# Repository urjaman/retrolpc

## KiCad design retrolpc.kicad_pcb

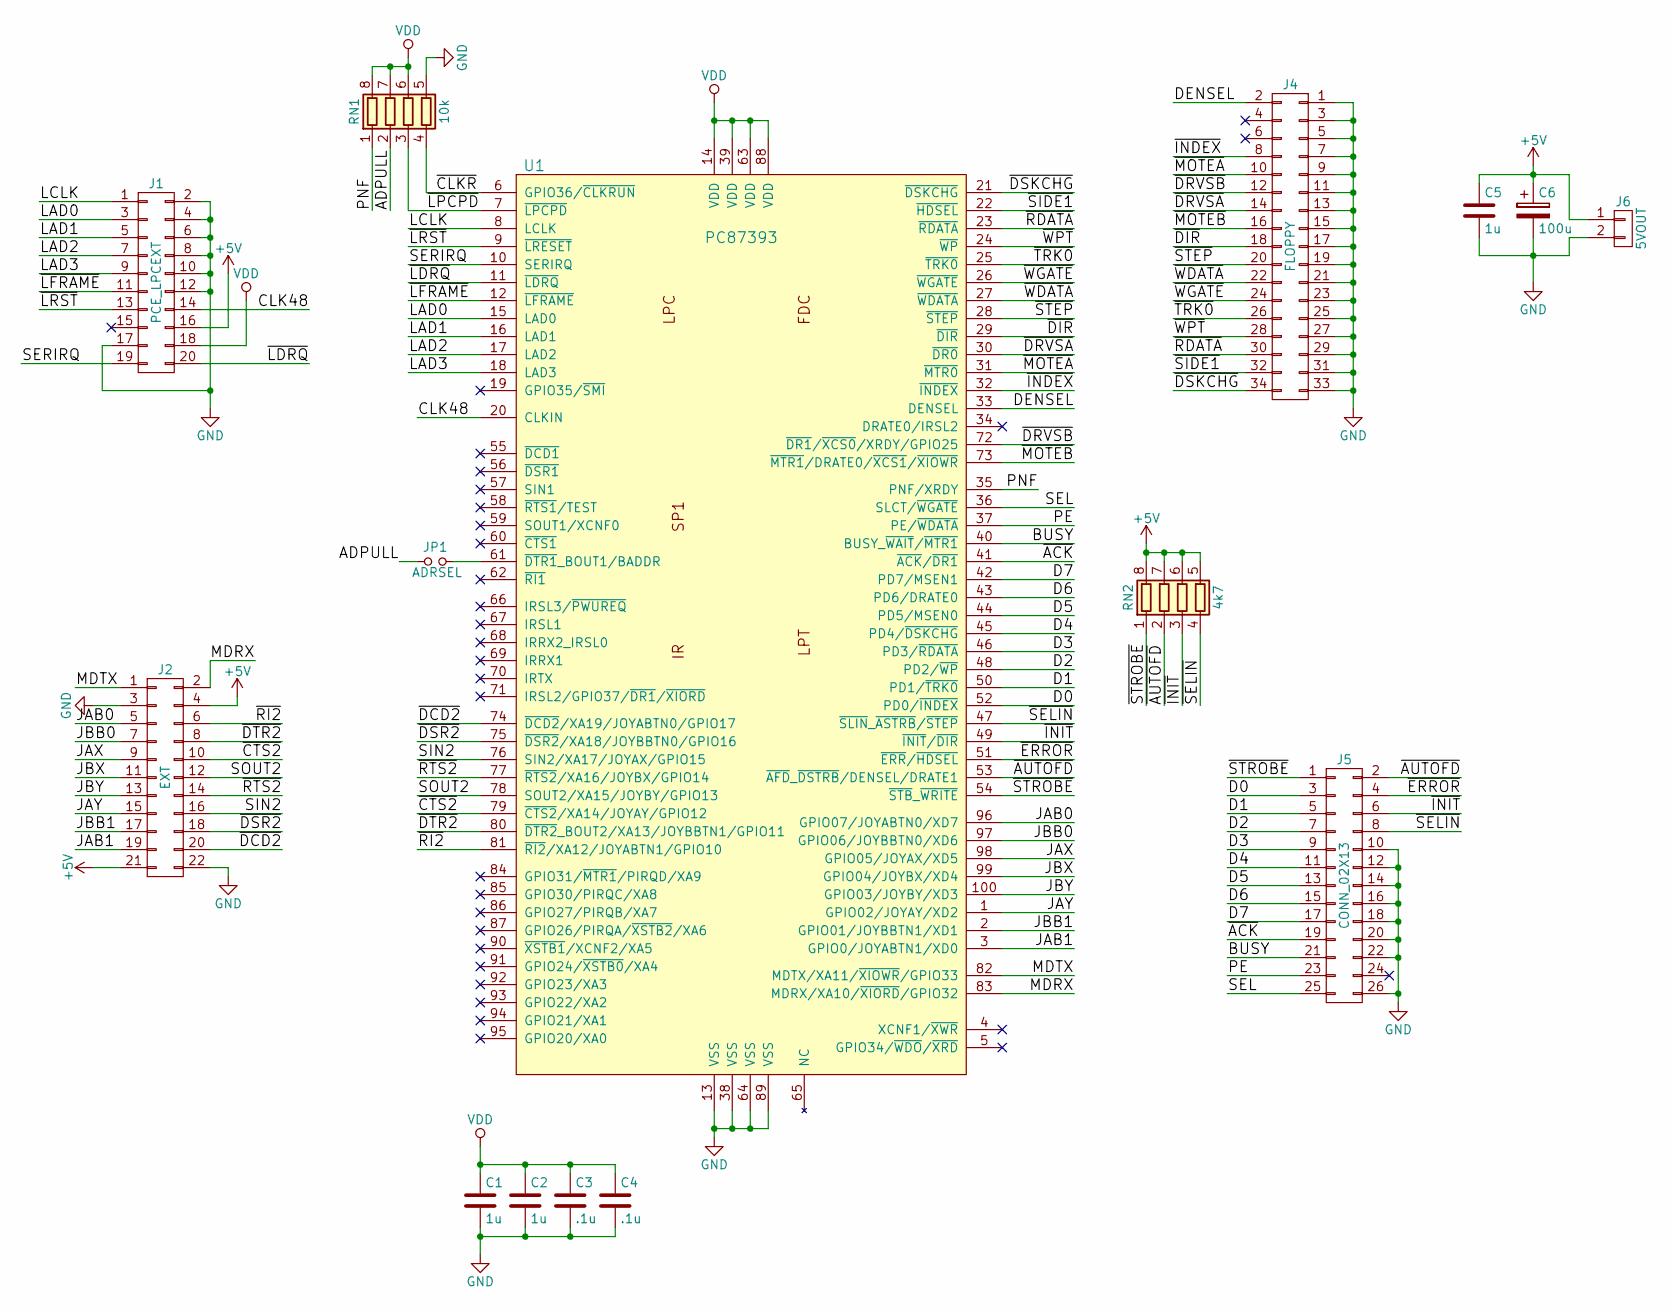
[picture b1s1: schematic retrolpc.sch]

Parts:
C1, C2, C5: 1u; C_0805_HandSoldering
C3, C4: .1u; C_0603_HandSoldering
C6: 100u; CP_Radial_D8.0mm_P3.50mm
J1: PCE_LPCEXT; Socket_Strip_Straight_2x10_Pitch2.54mm
J2: EXT; Pin_Header_Straight_2x11_Pitch2.54mm
J4: FLOPPY; Pin_Header_Straight_2x17_Pitch2.54mm
J5: CONN_02X13; Pin_Header_Straight_2x13_Pitch2.54mm
J6: 5VOUT; TerminalBlock_Pheonix_PT-3.5mm_2pol
JP1: ADRSEL; Pin_Header_Straight_1x02_Pitch2.54mm
RN1: 10k; R_Array_Convex_4x0603
RN2: 4k7; R_Array_Convex_4x0603
U1: PC87393; TQFP-100_14x14mm_Pitch0.5mm

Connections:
+5V: C5.1, C6.1, J1.16, J2.4, J2.21, J6.1, RN2.5 (R4.2), RN2.6 (R3.2), RN2.7 (R2.2), RN2.8 (R1.2)
/ADPULL: JP1.1, RN1.2 (R2.1)
/BUSY: J5.21, U1.40 (BUSY_~WAIT~/~MTR1)
/CLK48: J1.14, U1.20 (CLKIN)
/D0: J5.3, U1.52 (PD0/~INDEX)
/D1: J5.5, U1.50 (PD1/~TRK0)
/D2: J5.7, U1.48 (PD2/~WP)
/D3: J5.9, U1.46 (PD3/~RDATA)
/D4: J5.11, U1.45 (PD4/~DSKCHG)
/D5: J5.13, U1.44 (PD5/MSEN0)
/D6: J5.15, U1.43 (PD6/DRATE0)
/D7: J5.17, U1.42 (PD7/MSEN1)
/DENSEL: J4.2, U1.33 (DENSEL)
/JAB0: J2.5, U1.96 (GPIO07/JOYABTN0/XD7)
/JAB1: J2.19, U1.3 (GPIO0/JOYABTN1/XD0)
/JAX: J2.9, U1.98 (GPIO05/JOYAX/XD5)
/JAY: J2.15, U1.1 (GPIO02/JOYAY/XD2)
/JBB0: J2.7, U1.97 (GPIO06/JOYBBTN0/XD6)
/JBB1: J2.17, U1.2 (GPIO01/JOYBBTN1/XD1)
/JBX: J2.11, U1.99 (GPIO04/JOYBX/XD4)
/JBY: J2.13, U1.100 (GPIO03/JOYBY/XD3)
/LAD0: J1.3, U1.15 (LAD0)
/LAD1: J1.5, U1.16 (LAD1)
/LAD2: J1.7, U1.17 (LAD2)
/LAD3: J1.9, U1.18 (LAD3)
/LCLK: J1.1, U1.8 (LCLK)
/MDRX: J2.2, U1.83 (MDRX/XA10/~XIORD~/GPIO32)
/MDTX: J2.1, U1.82 (MDTX/XA11/~XIOWR~/GPIO33)
/PE: J5.23, U1.37 (PE/~WDATA)
/PNF: RN1.1 (R1.1), U1.35 (PNF/XRDY)
/SEL: J5.25, U1.36 (SLCT/~WGATE)
/SERIRQ: J1.19, U1.10 (SERIRQ)
/SIN2: J2.16, U1.76 (SIN2/XA17/JOYAX/GPIO15)
/SOUT2: J2.12, U1.78 (SOUT2/XA15/JOYBY/GPIO13)
/~ACK: J5.19, U1.41 (~ACK~/~DR1)
/~AUTOFD: J5.2, RN2.2 (R2.1), U1.53 (~AFD~_~DSTRB~/DENSEL/DRATE1)
/~CLKR: RN1.4 (R4.1), U1.6 (GPIO36/~CLKRUN)
/~CTS2: J2.10, U1.79 (~CTS2~/XA14/JOYAY/GPIO12)
/~DCD2: J2.20, U1.74 (~DCD2~/XA19/JOYABTN0/GPIO17)
/~DIR: J4.18, U1.29 (~DIR)
/~DRVSA: J4.14, U1.30 (~DR0)
/~DRVSB: J4.12, U1.72 (~DR1~/~XCS0~/XRDY/GPIO25)
/~DSKCHG: J4.34, U1.21 (~DSKCHG)
/~DSR2: J2.18, U1.75 (~DSR2~/XA18/JOYBBTN0/GPIO16)
/~DTR2: J2.8, U1.80 (~DTR2~_BOUT2/XA13/JOYBBTN1/GPIO11)
/~ERROR: J5.4, U1.51 (~ERR~/~HDSEL)
/~INDEX: J4.8, U1.32 (~INDEX)
/~INIT: J5.6, RN2.3 (R3.1), U1.49 (~INIT~/~DIR)
/~LDRQ: J1.20, U1.11 (~LDRQ)
/~LFRAME: J1.11, U1.12 (~LFRAME)
/~LPCPD: RN1.3 (R3.1), U1.7 (~LPCPD)
/~LRST: J1.13, U1.9 (~LRESET)
/~MOTEA: J4.10, U1.31 (~MTR0)
/~MOTEB: J4.16, U1.73 (~MTR1~/DRATE0/~XCS1~/~XIOWR)
/~RDATA: J4.30, U1.23 (~RDATA)
/~RI2: J2.6, U1.81 (~RI2~/XA12/JOYABTN1/GPIO10)
/~RTS2: J2.14, U1.77 (~RTS2~/XA16/JOYBX/GPIO14)
/~SELIN: J5.8, RN2.4 (R4.1), U1.47 (~SLIN~_~ASTRB~/~STEP)
/~SIDE1: J4.32, U1.22 (~HDSEL)
/~STEP: J4.20, U1.28 (~STEP)
/~STROBE: J5.1, RN2.1 (R1.1), U1.54 (~STB~_~WRITE)
/~TRK0: J4.26, U1.25 (~TRK0)
/~WDATA: J4.22, U1.27 (~WDATA)
/~WGATE: J4.24, U1.26 (~WGATE)
/~WPT: J4.28, U1.24 (~WP)
GND: C1.2, C2.2, C3.2, C4.2, C5.2, C6.2, J1.2, J1.4, J1.6, J1.8, J1.10, J1.12, J1.17, J2.3, J2.22, J4.1, J4.3, J4.5, J4.7, J4.9, J4.11, J4.13, J4.15, J4.17, J4.19, J4.21, J4.23, J4.25, J4.27, J4.29, J4.31, J4.33, J5.10, J5.12, J5.14, J5.16, J5.18, J5.20, J5.22, J5.26, J6.2, RN1.5 (R4.2), U1.13 (VSS), U1.38 (VSS), U1.64 (VSS), U1.89 (VSS)
unnamed: JP1.2, U1.61 (~DTR1~_BOUT1/BADDR)
VDD: C1.1, C2.1, C3.1, C4.1, J1.18, RN1.6 (R3.2), RN1.7 (R2.2), RN1.8 (R1.2), U1.14 (VDD), U1.39 (VDD), U1.63 (VDD), U1.88 (VDD)

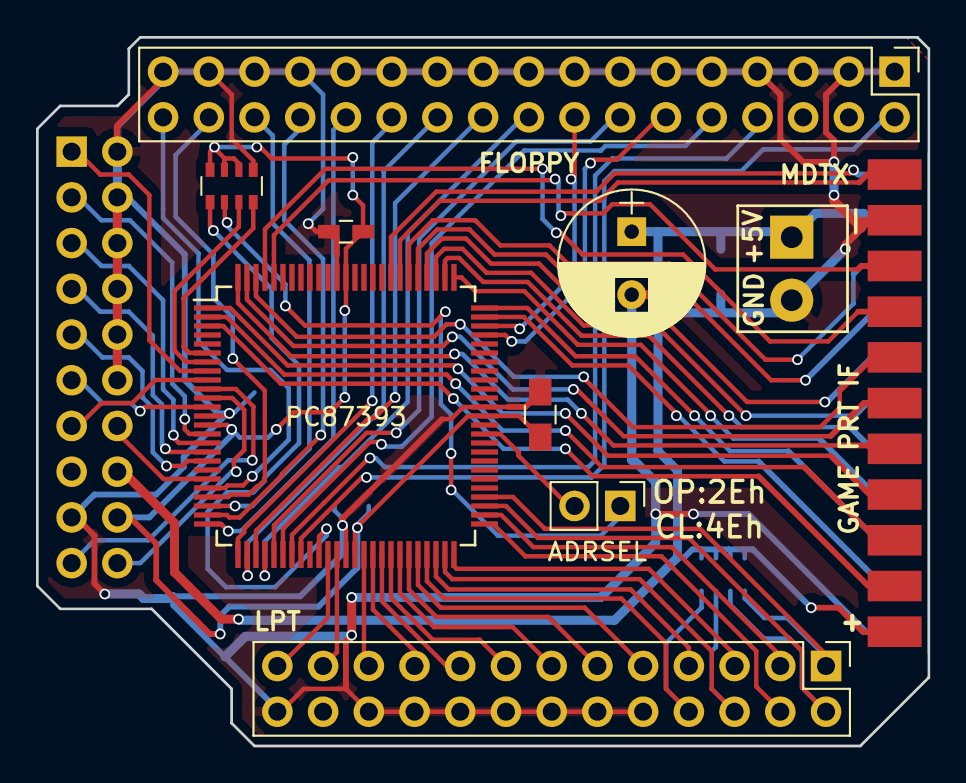
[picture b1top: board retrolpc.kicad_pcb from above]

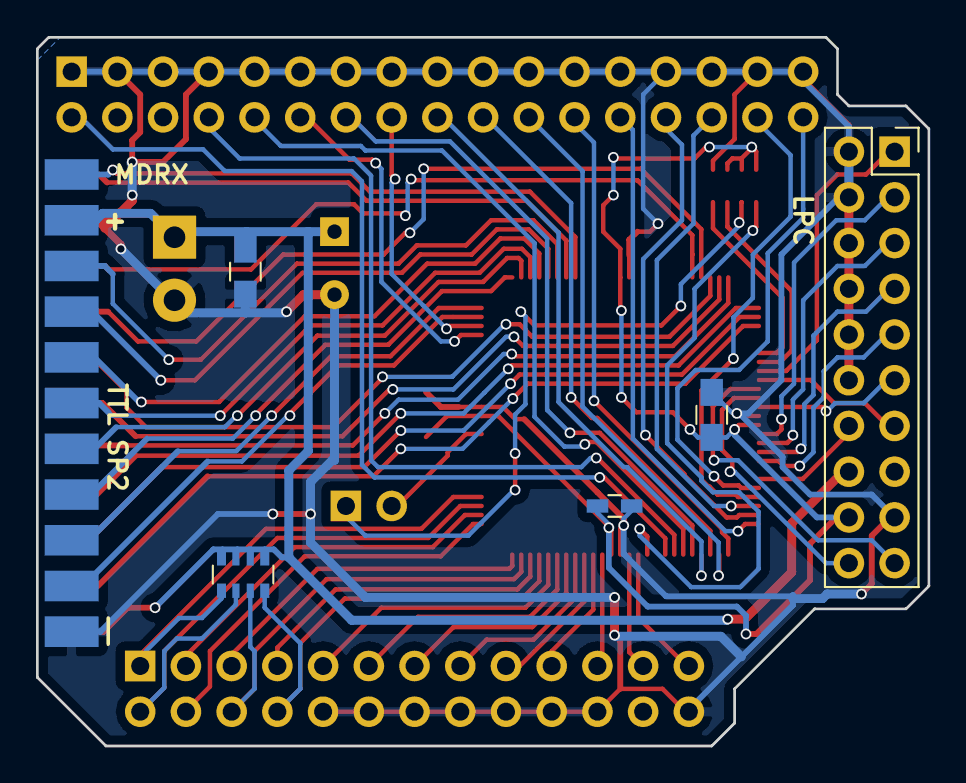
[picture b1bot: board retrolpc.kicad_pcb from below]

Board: 2 copper layers, 49.5 x 39.4 mm, 15 parts (5 on the bottom side), 68 nets.

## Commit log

2017-08-30 Initial commit with the first ordered version
